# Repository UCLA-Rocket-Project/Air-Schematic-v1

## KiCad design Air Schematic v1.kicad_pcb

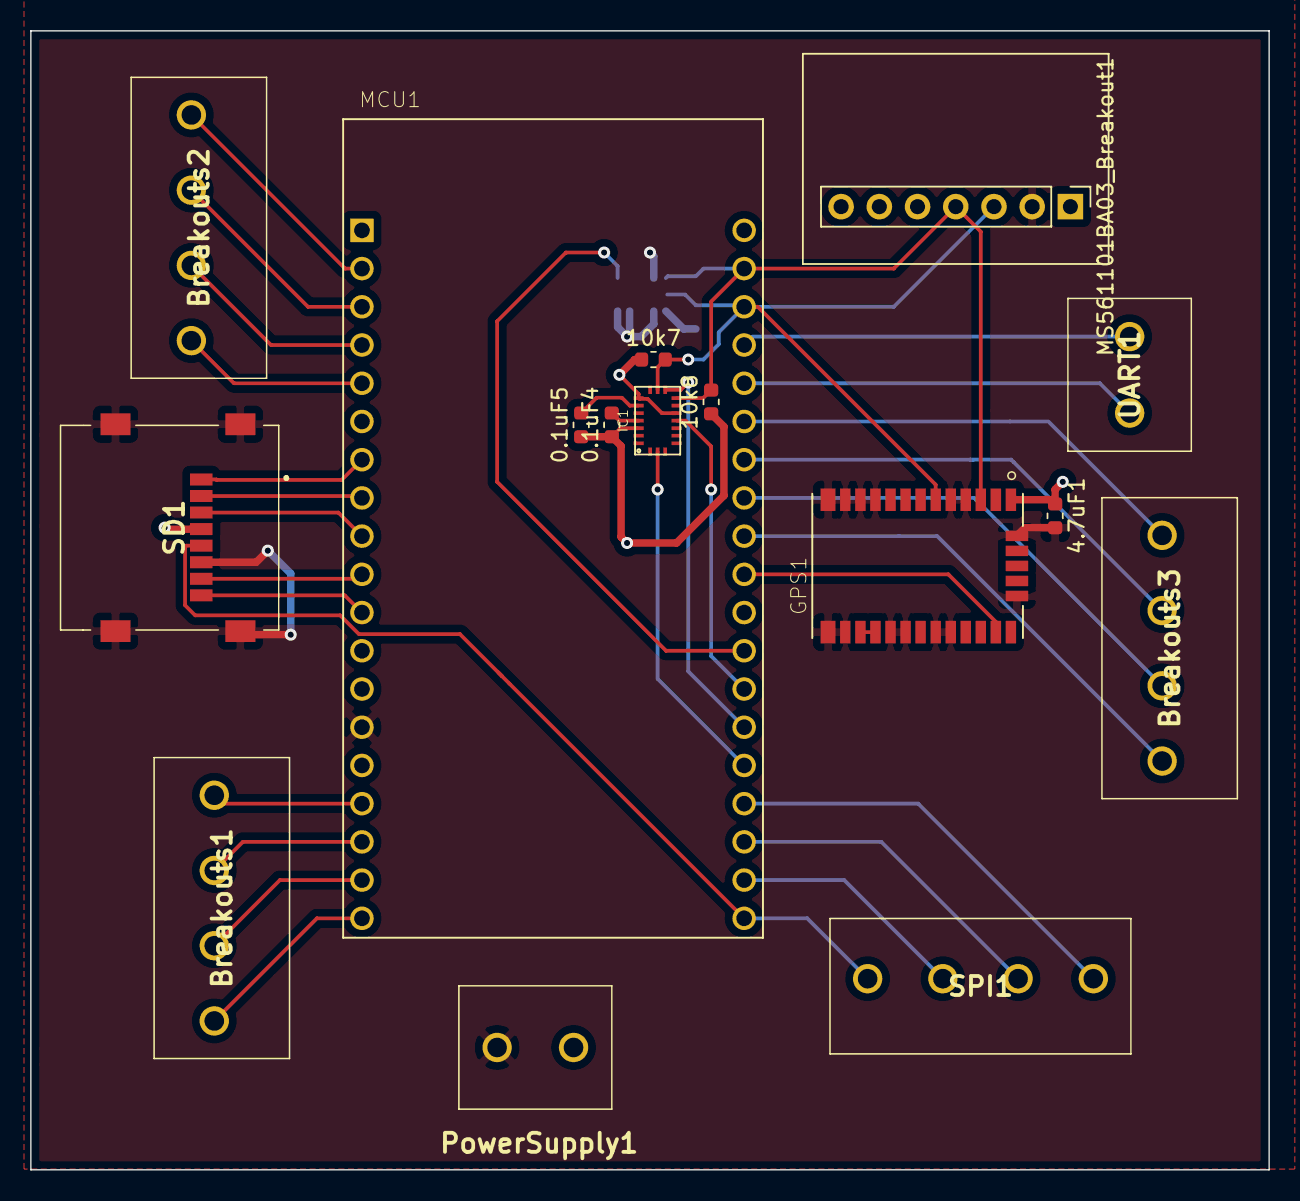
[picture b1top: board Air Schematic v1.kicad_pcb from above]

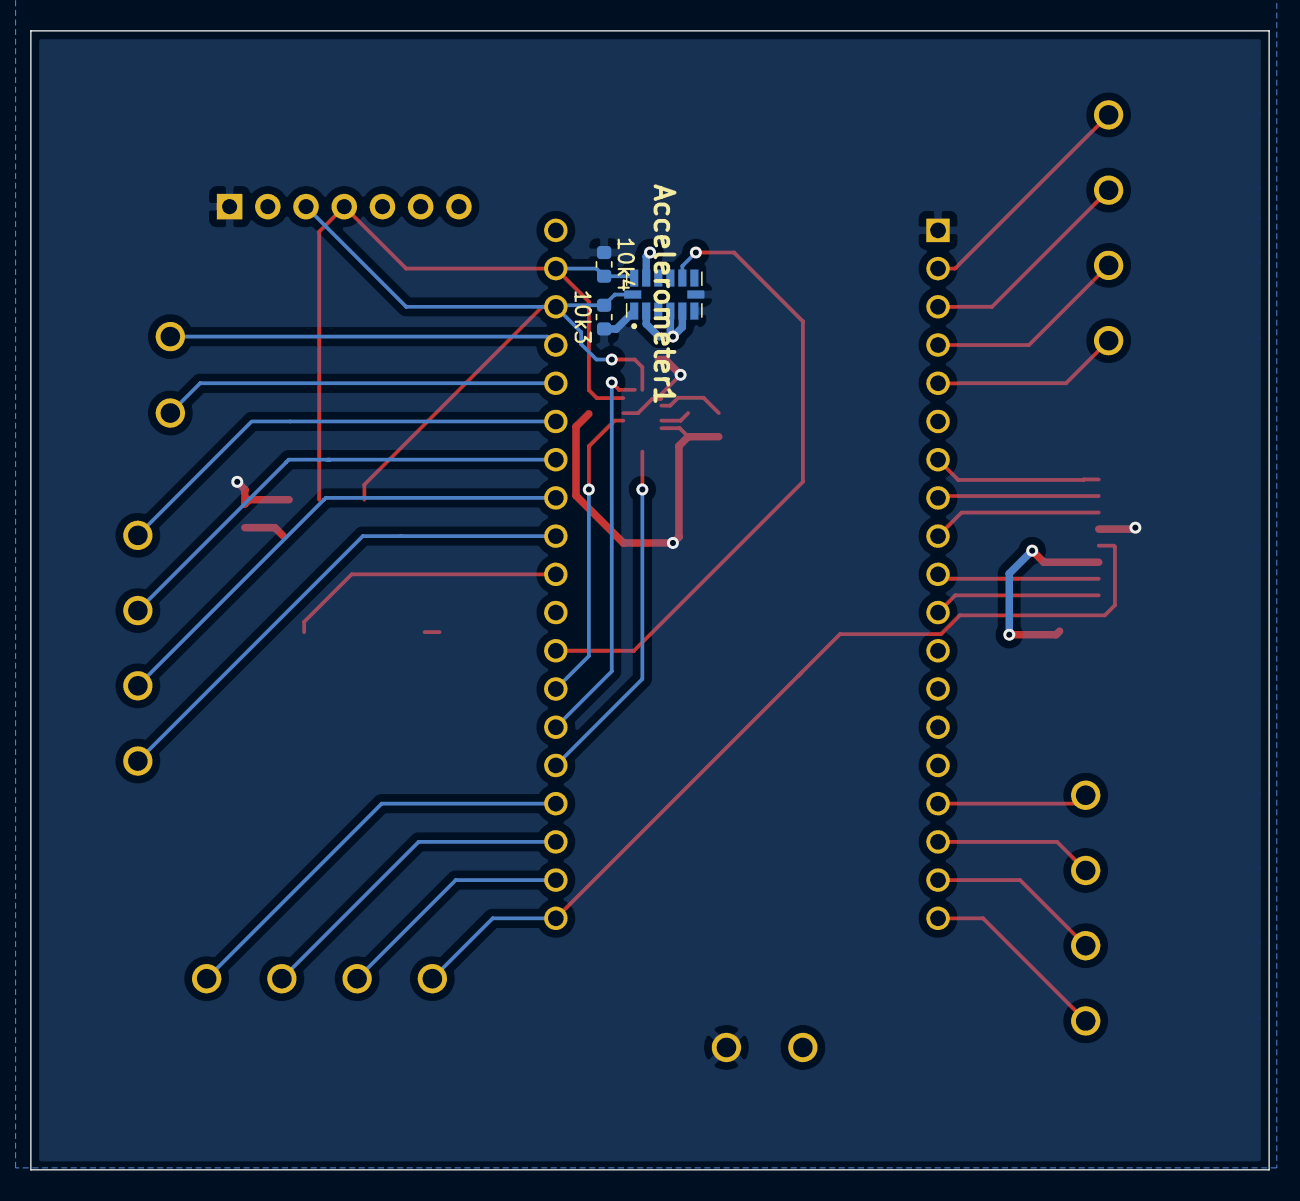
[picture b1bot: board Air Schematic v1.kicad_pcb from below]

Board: 2 copper layers, 82.3 x 75.7 mm, 19 parts (3 on the bottom side), 35 nets.

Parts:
0.1uF4, 0.1uF5, 4.7uF1: C; C_0603_1608Metric
10k3, 10k4, 10k7, 10k8: R; R_0603_1608Metric
Accelerometer1: ADXL375BCCZ; CC-14-1
Breakouts1, Breakouts2, Breakouts3: TB001-500-04BE; TB00150004BE
GPS1: CAM-M8Q-0; LCC100P960X1400X210-31N
IC1: BMX055
MCU1: ESP32-DEVKITC-32D; MODULE_ESP32-DEVKITC-32D
MS561101BA03_Breakout1: Altimeter; Inexact_Altimeter_Breakout
PowerSupply1: TB006-508-02BE; TB00650802BE
SD1: 47219-2001; 472192001
SPI1: TB001-500-04BE; TB00150004BE
UART1: TB006-508-02BE; TB00650802BE

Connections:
+3V3: 0.1uF4.1, 0.1uF5.1, 4.7uF1.1, 10k3.1, 10k4.1, 10k7.1, 10k8.1, Accelerometer1.1, Accelerometer1.6, Accelerometer1.7, GPS1.1, GPS1.8, GPS1.9, IC1.3, IC1.7, IC1.13, MCU1.1, MS561101BA03_Breakout1.1, PowerSupply1.1, SD1.4
ACCEL2_READY: IC1.19, MCU1.34
ACCEL_READY: Accelerometer1.9, MCU1.31
CLK: MCU1.38, SD1.5, SPI1.4
CMD: MCU1.9, SD1.3
CS: MCU1.35, SPI1.1
Dat0: MCU1.10, SD1.7
Dat1: MCU1.11, SD1.8
Dat2: MCU1.7, SD1.1
Dat3: MCU1.8, SD1.2
GND: 4.7uF1.2, Accelerometer1.2, Accelerometer1.4, Accelerometer1.5, Accelerometer1.12, GPS1.4, GPS1.5, GPS1.10, GPS1.11, GPS1.12, GPS1.13, GPS1.14, GPS1.15, GPS1.18, GPS1.19, GPS1.21, GPS1.22, GPS1.27, GPS1.31, MCU1.14, MS561101BA03_Breakout1.2, PowerSupply1.2, SD1.6, SD1.9, SD1.10, SD1.11, SD1.12
GPS_READY: GPS1.25, MCU1.29
GYRO_READY: IC1.10, MCU1.33
MAGNET_READY: IC1.14, MCU1.32
MISO: MCU1.36, SPI1.2
MOSI: MCU1.37, SPI1.3
unnamed: 0.1uF4.2, IC1.4
unnamed: 0.1uF5.2, IC1.6
unnamed: Breakouts1.1, MCU1.16
unnamed: Breakouts1.2, MCU1.17
unnamed: Breakouts1.3, MCU1.18
unnamed: Breakouts1.4, MCU1.19
unnamed: Breakouts2.1, MCU1.2
unnamed: Breakouts2.2, MCU1.3
unnamed: Breakouts2.3, MCU1.4
unnamed: Breakouts2.4, MCU1.5
unnamed: Breakouts3.1, MCU1.25
unnamed: Breakouts3.2, MCU1.26
unnamed: Breakouts3.3, MCU1.27
unnamed: Breakouts3.4, MCU1.28
unnamed: GPS1.16, GPS1.17
RX: MCU1.24, UART1.2
SCLK: 10k3.2, 10k7.2, Accelerometer1.14, GPS1.6, IC1.9, MCU1.22, MS561101BA03_Breakout1.3
SDA: 10k4.2, 10k8.2, Accelerometer1.13, GPS1.3, IC1.11, MCU1.21, MS561101BA03_Breakout1.4
TX: MCU1.23, UART1.1

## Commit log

2020-08-22 Add parts libraries
2020-09-05 Added footprints, initial pcb layouts
2020-09-10 Switched out altimeter and IMU
2020-09-28 Updated schematic, pcb, a really messy bom
2020-10-03 Reorganized files
